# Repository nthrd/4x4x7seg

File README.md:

########################
# 4x4x7Segment Display #
########################

This is a small board with a lot of digits. Featuring four [HP  4-digit 7-segment  bubble displays][1] on a board designed to be mated with the [Adafruit HT16K33 breakout][2], this will quickly allow you to display four values using i^(2)c.

Mounting:

* Solder a right angle header strip to the bottom header for vertical mounting.
* Solder straight header strips to the bottom or both headers for horizontal mounting.
* The top header is not electrically connected and is for more stable horizontal mounting.

[1]: https://www.sparkfun.com/products/12710 "SparkFun product page."
[2]: https://www.adafruit.com/product/1427 "Adafruit product page."

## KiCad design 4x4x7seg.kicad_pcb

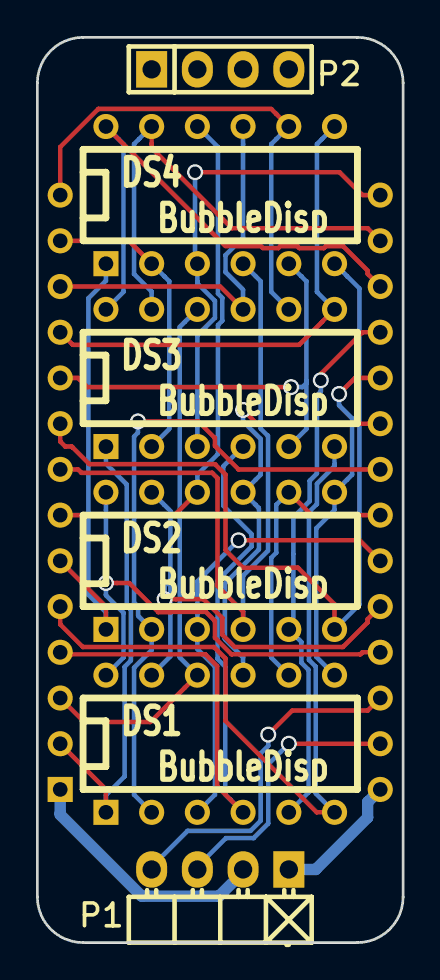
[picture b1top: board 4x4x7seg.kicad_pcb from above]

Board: 2 copper layers, 20.3 x 50.3 mm, 7 parts (1 on the bottom side), 28 nets.

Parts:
A1: AdaFruit_HT16K33; DIP-28__700
DS1, DS2, DS3, DS4: BubbleDisp; DIP-12__300
P1: CONN_4; Pin_Header_Angled_1x04
P2: CONN_4; Pin_Header_Straight_1x04

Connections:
/A0: A1.25, DS1.12, DS2.12
/A1: A1.24, DS1.11, DS2.11
/A2: A1.23, DS1.3, DS2.3
/A3: A1.22, DS1.8, DS2.8
/A4: A1.21, DS1.2, DS2.2
/A5: A1.20, DS1.9, DS2.9
/A6: A1.19, DS1.7, DS2.7
/A7: A1.18, DS1.5, DS2.5
/A8: A1.17, DS3.12, DS4.12
/A9: A1.16, DS3.11, DS4.11
/A10: A1.15, DS3.3, DS4.3
/A11: A1.14, DS3.8, DS4.8
/A12: A1.13, DS3.2, DS4.2
/A13: A1.12, DS3.9, DS4.9
/A14: A1.11, DS3.7, DS4.7
/A15: A1.10, DS3.5, DS4.5
/C0: A1.2, DS1.1, DS3.1
/C1: A1.3, DS1.10, DS3.10
/C2: A1.4, DS1.4, DS3.4
/C3: A1.5, DS1.6, DS3.6
/C4: A1.6, DS2.1, DS4.1
/C5: A1.7, DS2.10, DS4.10
/C6: A1.8, DS2.4, DS4.4
/C7: A1.9, DS2.6, DS4.6
unnamed: A1.1, P1.2
unnamed: A1.26, P1.4
unnamed: A1.27, P1.3
unnamed: A1.28, P1.1

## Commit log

2014-08-26 Initial Commit.
2014-08-26 Captial, GitHub...
